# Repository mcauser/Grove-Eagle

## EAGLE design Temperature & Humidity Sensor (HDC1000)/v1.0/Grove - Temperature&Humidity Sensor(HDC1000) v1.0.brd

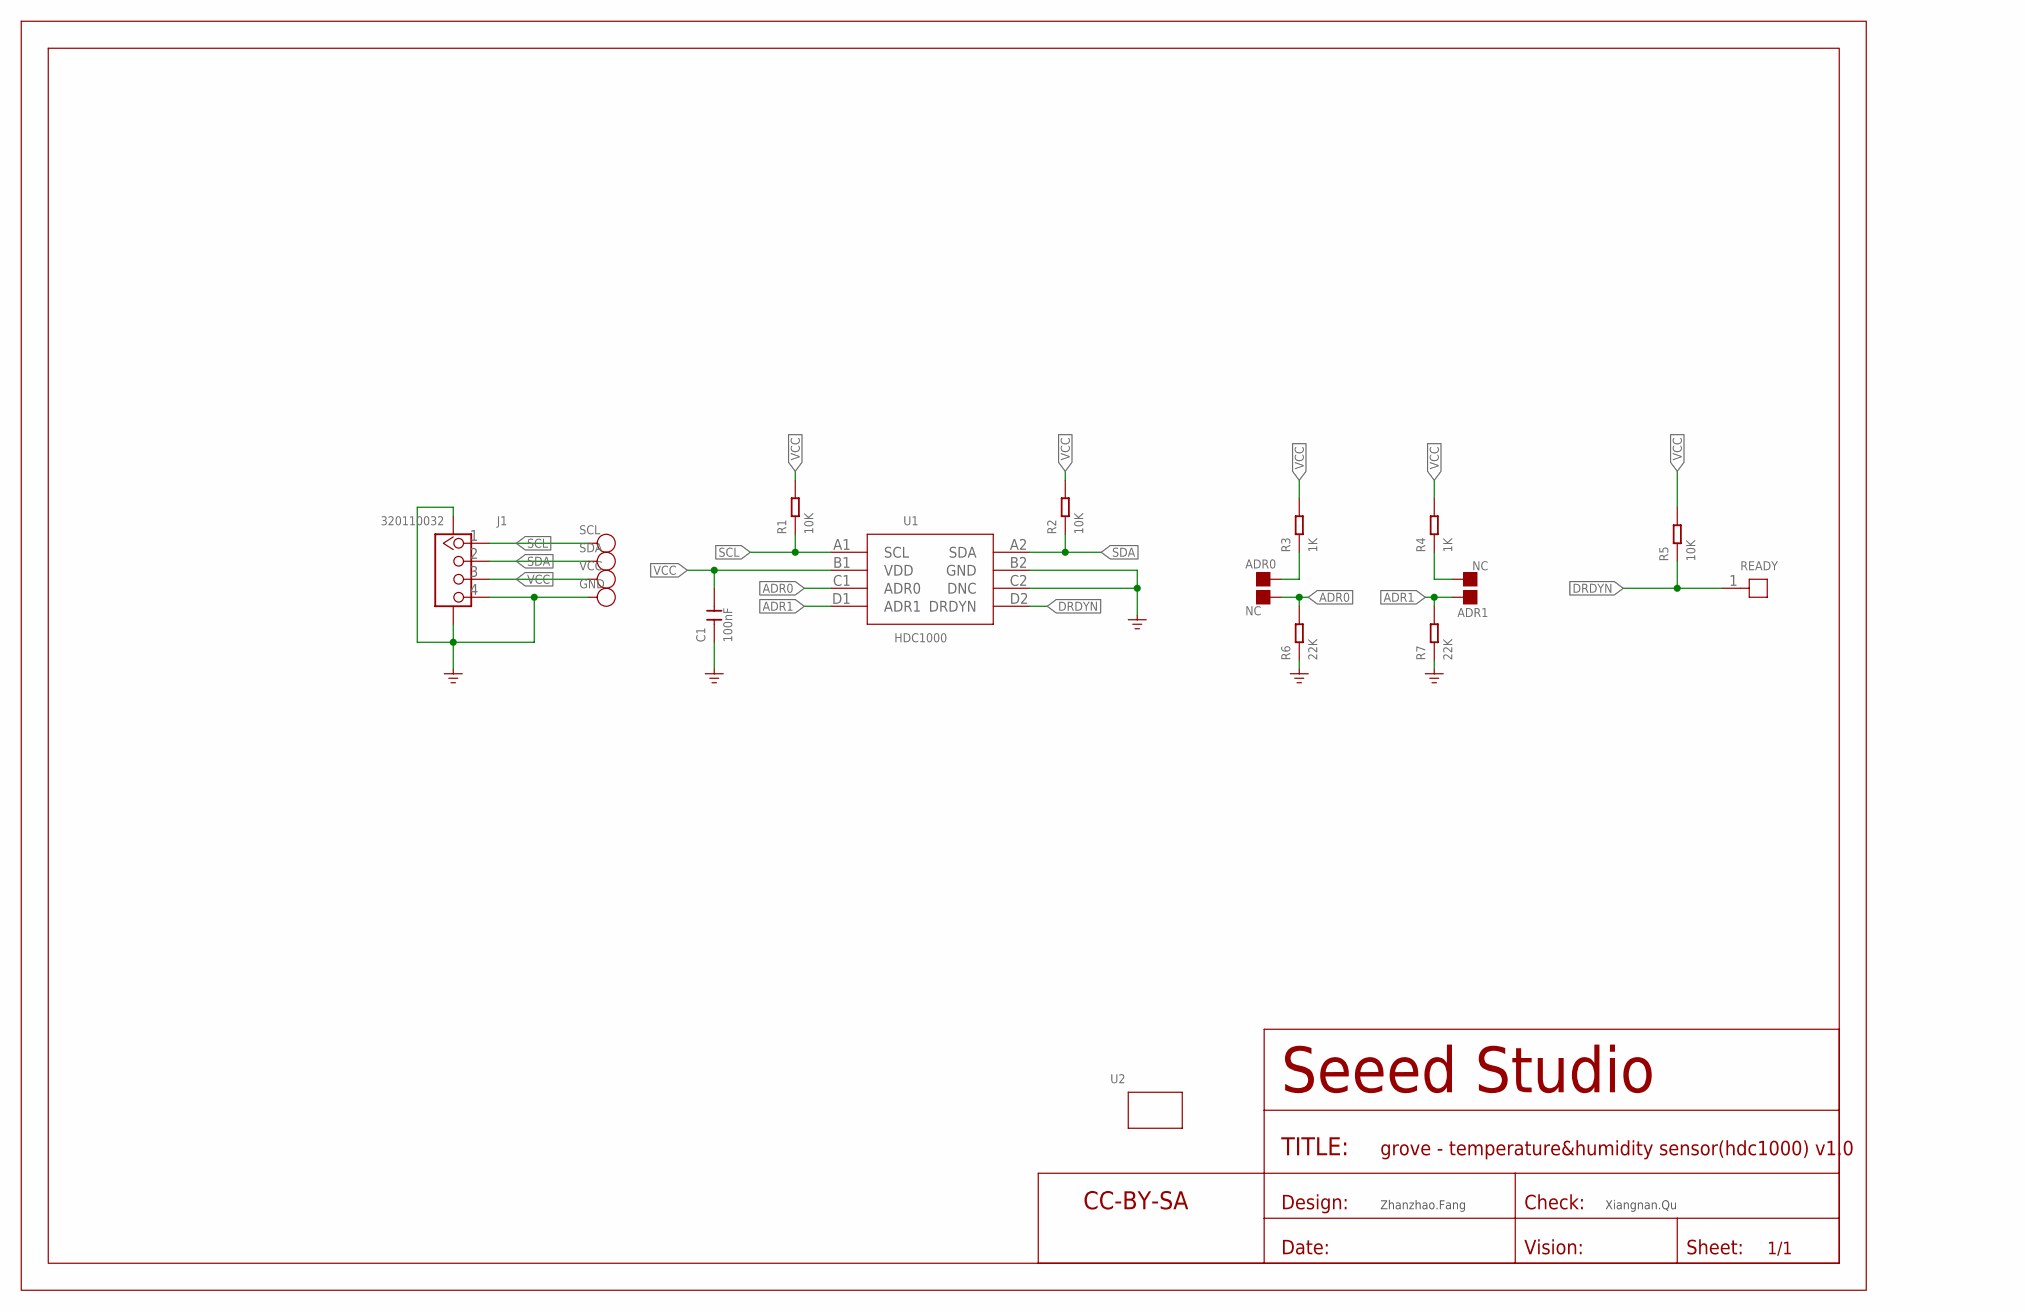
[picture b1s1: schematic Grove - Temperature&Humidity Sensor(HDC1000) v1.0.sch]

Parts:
ADR0, ADR1: NC; JUMPER-2P
C1: 100nF; C0603
GND: NC; TP-D45MIL
J1: 320110032; HW4-SMD-2.0-90D
R1, R2, R5: 10K; R0603
R3, R4: 1K; R0603
R6, R7: 22K; R0603
READY: HEADER-1P-40; 1P-80/40MIL
SCL: NC; TP-D45MIL
SDA: NC; TP-D45MIL
U1: HDC1000; SNR8-SMD-0.5-2.04X1.59MM
U2: GROVE'2U'; GROVE-1*2-TEST-PLATFORM
U$4: SEEEDSTUDIO-OPEN-SCH-FRAME; SEEEDSTUDIO-PCB-FRAME
VCC: NC; TP-D45MIL

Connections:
ADR0: ADR0.1, R6.2, U1.C1 (ADR0)
ADR1: ADR1.2, R7.2, U1.D1 (ADR1)
DRDYN: R5.1, READY.1, U1.D2 (DRDYN)
GND: C1.1, GND.T, J1.4, J1.SS1, J1.SS2, R6.1, R7.1, U1.B2 (GND), U1.C2 (DNC)
unnamed: ADR0.2, R3.1
unnamed: ADR1.1, R4.1
SCL: J1.1, R1.1, SCL.T, U1.A1 (SCL)
SDA: J1.2, R2.1, SDA.T, U1.A2 (SDA)
VCC: C1.2, J1.3, R1.2, R2.2, R3.2, R4.2, R5.2, U1.B1 (VDD), VCC.T

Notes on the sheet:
Zhanzhao.Fang
Xiangnan.Qu

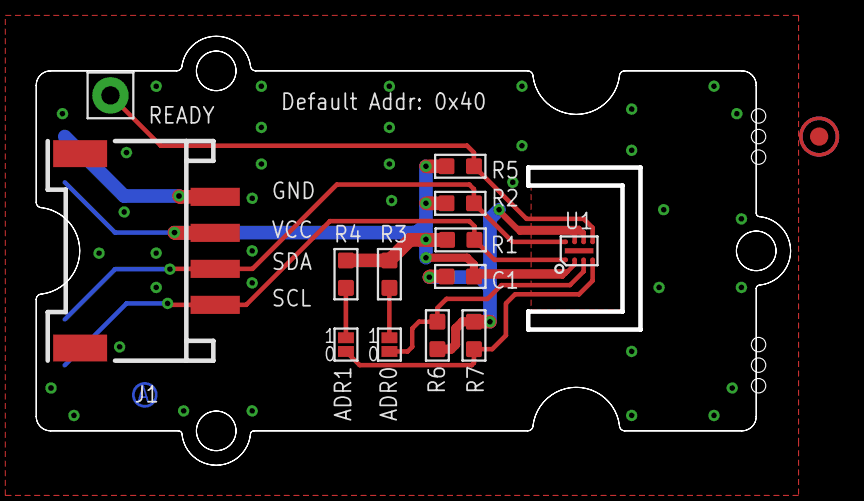
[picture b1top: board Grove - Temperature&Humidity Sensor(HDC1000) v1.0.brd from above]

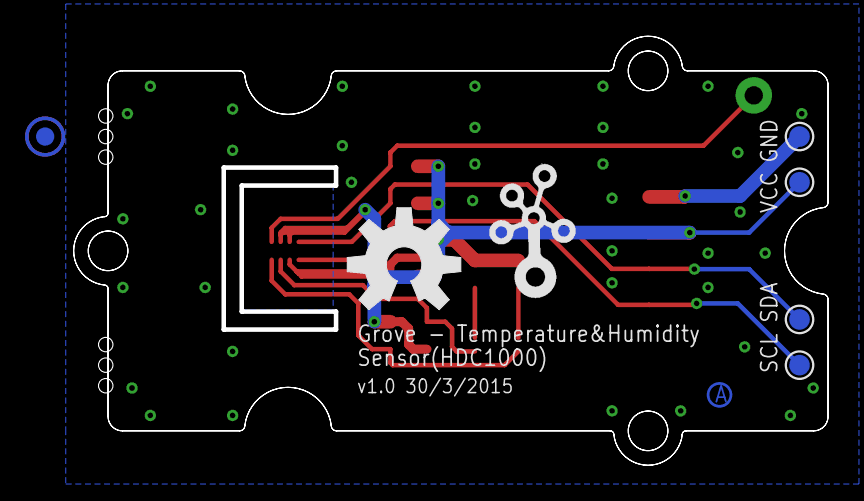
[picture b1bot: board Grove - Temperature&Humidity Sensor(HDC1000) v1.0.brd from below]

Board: 2 copper layers, 41.9 x 23.8 mm, 24 parts (7 on the bottom side), 9 nets.

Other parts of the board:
P4, P7: ROUND-MARK-1.0
U10: GROVE-TEST-PLATFORM
U$7: GROVE-SILK-BIG
U$10: OSHW_FILLX250_NOTEXT

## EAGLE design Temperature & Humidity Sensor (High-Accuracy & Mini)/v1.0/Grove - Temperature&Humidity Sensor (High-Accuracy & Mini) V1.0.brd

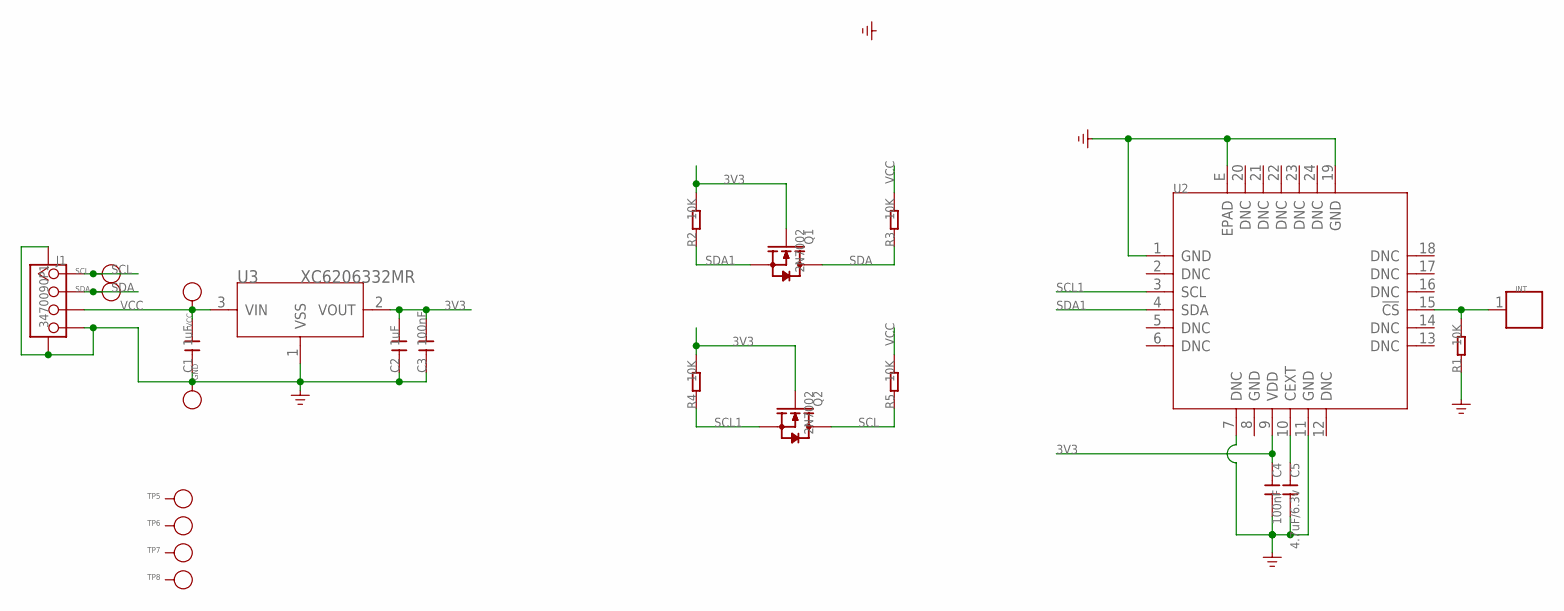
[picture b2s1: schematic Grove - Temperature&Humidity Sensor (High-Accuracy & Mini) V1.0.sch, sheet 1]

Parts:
C1, C2: 1uF; C0603
C3, C4: 100nF; C0603
C5: 4.7uF/6.3v; C0603
GND: PAD-TEST-POINT'4545'; TP_4545
INT: PAD'60/30'; 1P-65/35MIL
J1: 3470090P1; 4P-SMD-2.0
Q1, Q2: 2N7002; SOT23
R1, R2, R3, R4, R5: 10K; R0603
SCL: PAD-TEST-POINT'4545'; TP_4545
SDA: PAD-TEST-POINT'4545'; TP_4545
TP5, TP6, TP7, TP8: PAD-TEST-POINT'4545'; TP_4545
U2: SENSOR-TH02; QFN24
U3: XC6206332MR; SOT23
VCC: PAD-TEST-POINT'4545'; TP_4545

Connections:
3V3: C2.2, C3.2, C4.1, Q1.1 (G), Q2.1 (G), R2.2, R4.2, U2.9 (VDD), U3.2 (VOUT)
GND: C1.1, C2.1, C3.1, C4.2, C5.2, GND.T, J1.4, J1.SS1, J1.SS2, R1.1, U2.1 (GND), U2.7 (DNC), U2.11 (GND), U2.19 (GND), U2.E (EPAD), U3.1 (VSS)
unnamed: C5.1, U2.10 (CEXT)
unnamed: INT.1, R1.2, U2.15 (!CS)
SCL: J1.1, Q2.3 (D), R5.1, SCL.T
SCL1: Q2.2 (S), R4.1, U2.3 (SCL)
SDA: J1.2, Q1.3 (D), R3.1, SDA.T
SDA1: Q1.2 (S), R2.1, U2.4 (SDA)
VCC: C1.2, J1.3, R3.2, R5.2, U3.3 (VIN), VCC.T

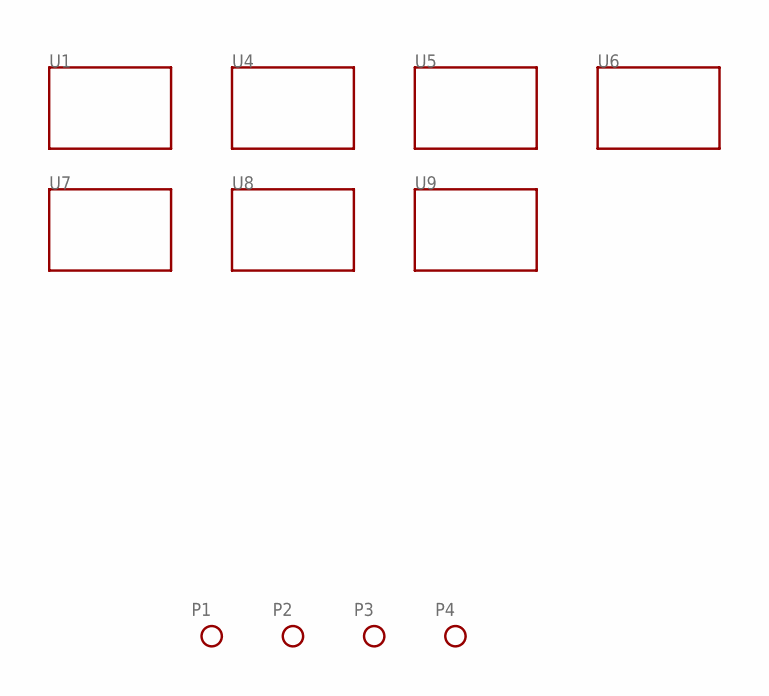
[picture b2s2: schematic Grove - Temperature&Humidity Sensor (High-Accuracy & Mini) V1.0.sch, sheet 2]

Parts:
P1, P2, P3, P4: PAD-MARK; ROUND-MARK-1.0
U1, U4, U5, U6, U7, U8, U9: TWIG'2U'; GROVE-TEST-PLATFORM

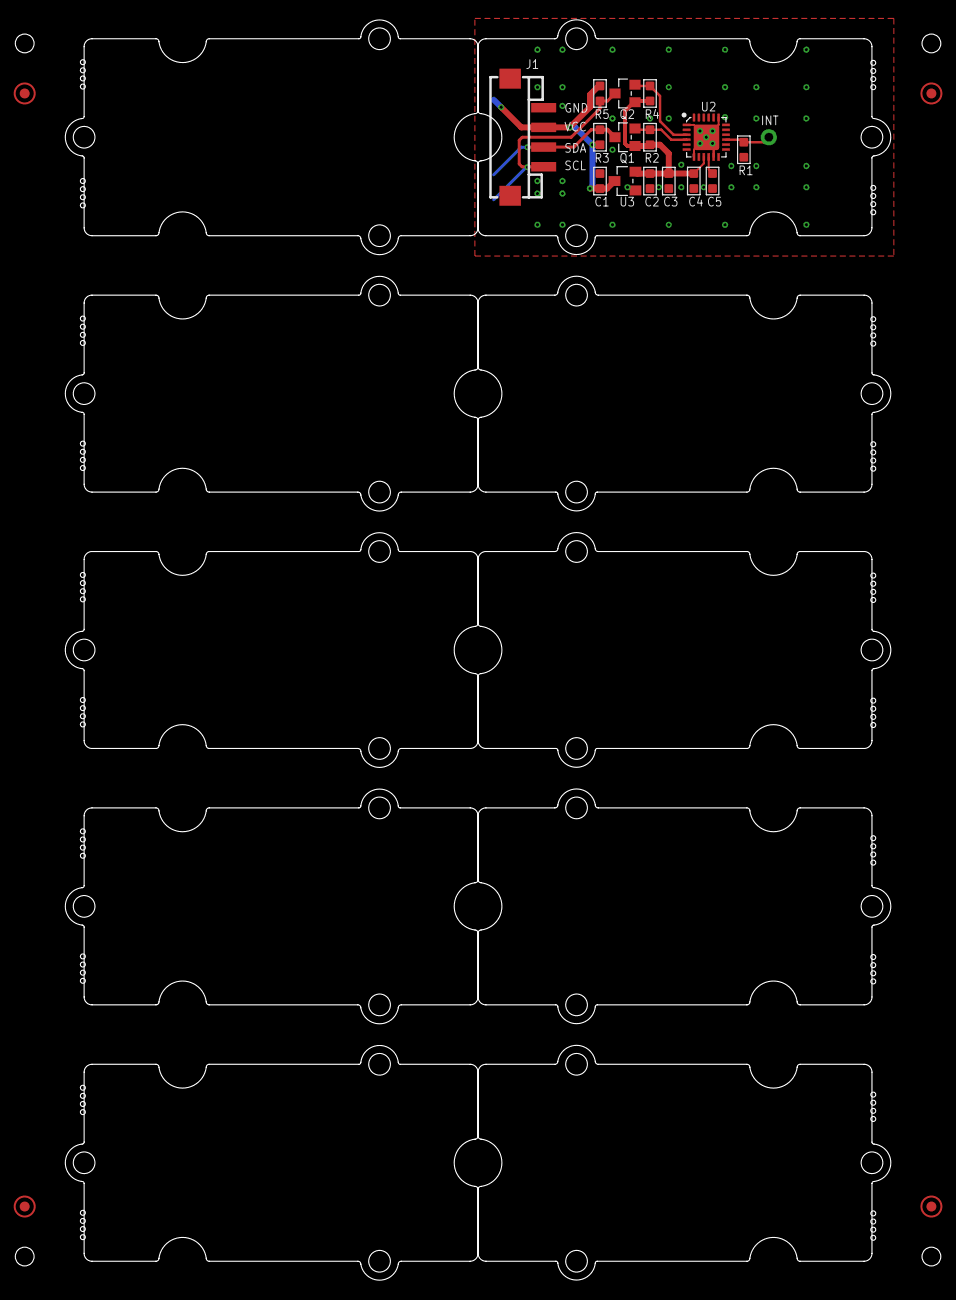
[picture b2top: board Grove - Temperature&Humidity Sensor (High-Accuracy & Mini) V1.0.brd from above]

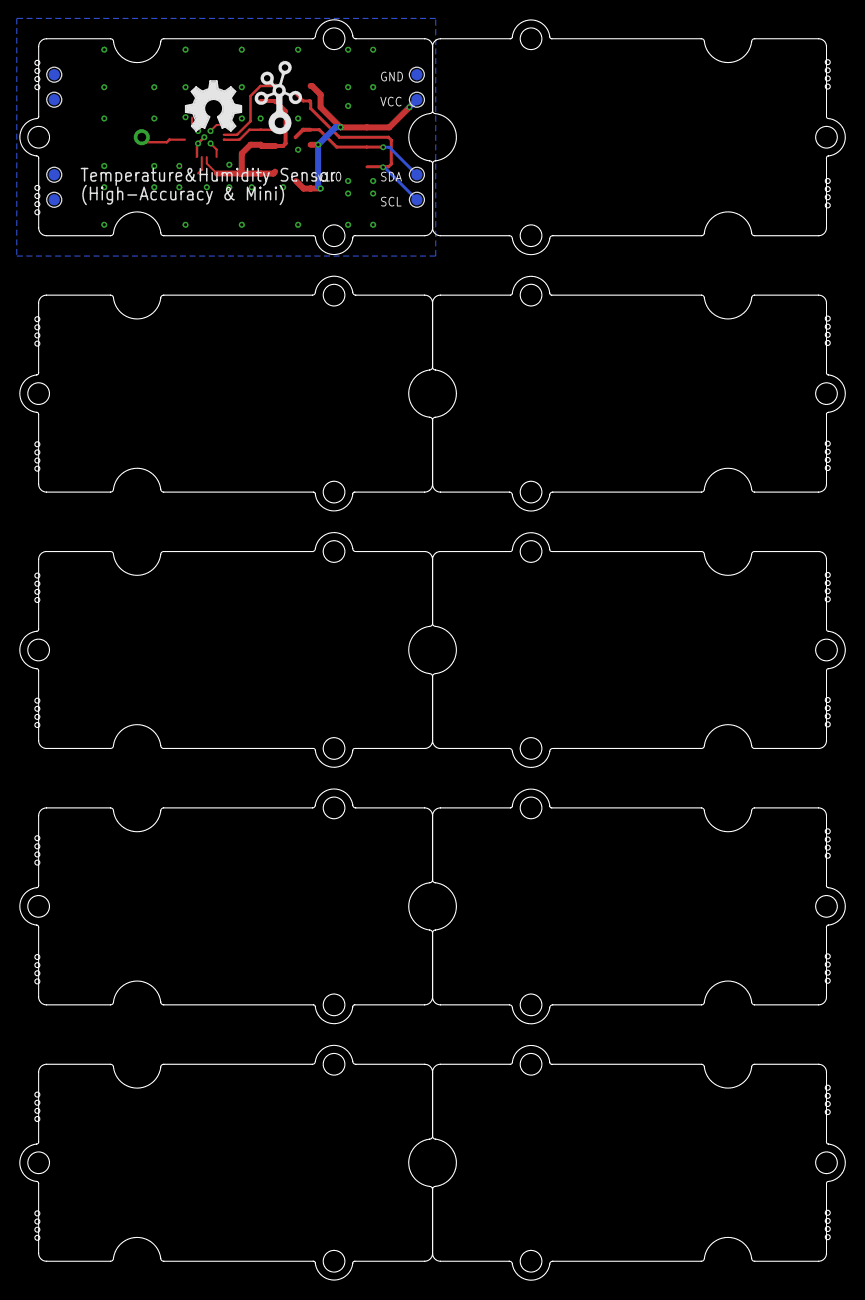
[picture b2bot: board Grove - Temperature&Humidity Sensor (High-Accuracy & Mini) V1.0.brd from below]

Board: 2 copper layers, 83.8 x 128.0 mm, 40 parts (10 on the bottom side), 9 nets.

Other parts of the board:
U11, U12: GROVE-TEST-PLATFORM@1
U$5: GROVE-2CONNECTOR-SMD
U$6: OSHW_FILLX200_NOTEXT
U$7: TWIGLOGO

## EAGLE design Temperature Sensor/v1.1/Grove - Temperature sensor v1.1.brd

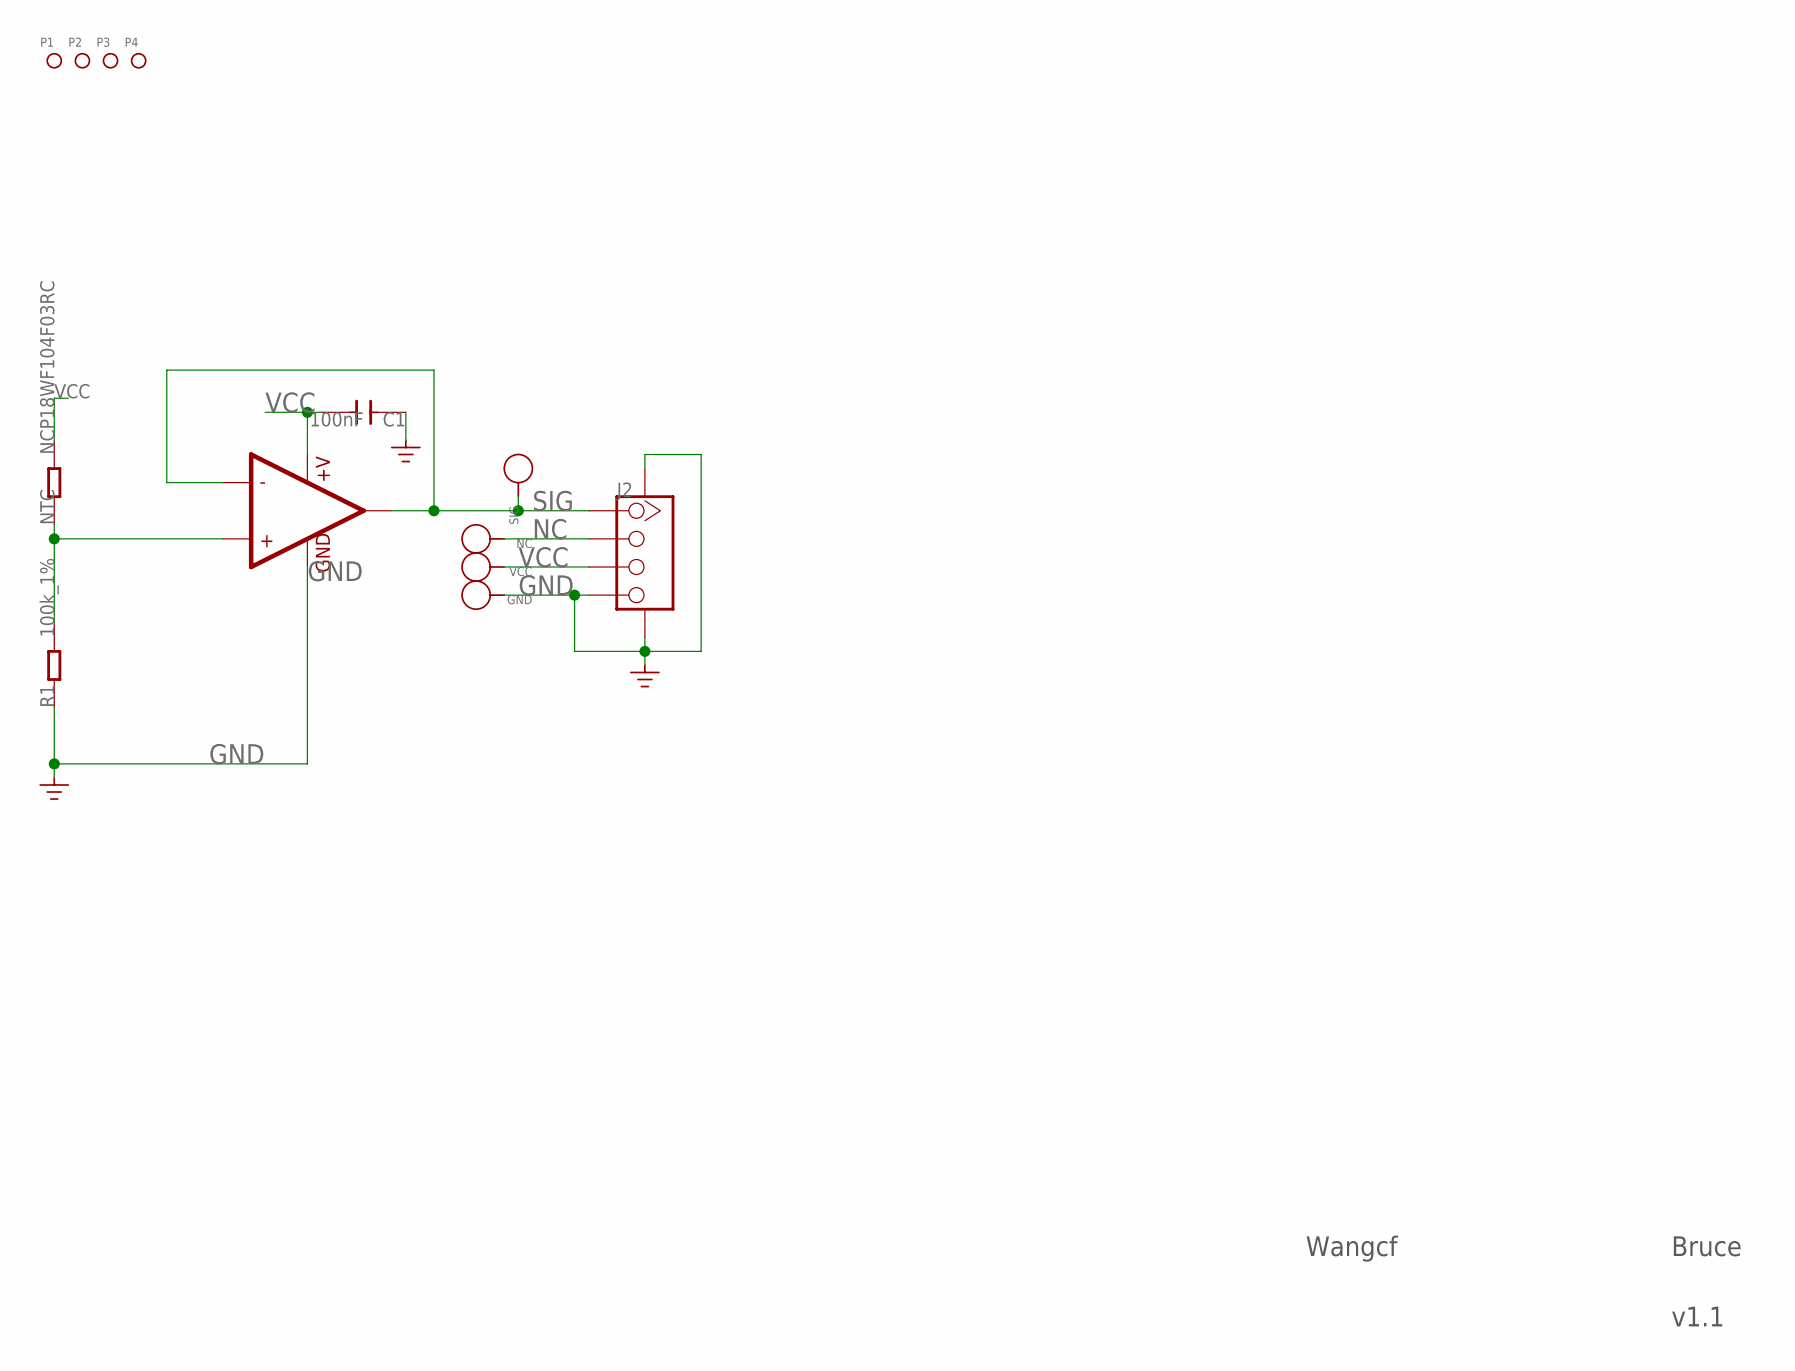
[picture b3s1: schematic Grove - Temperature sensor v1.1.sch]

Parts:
C1: 100nF; C0603
GND: PAD-TEST-POINT'4545'; TP_4545
J2: TWIG-4P-2.0-SMD-FEMALE-REINFORCE'DD'; 4P-SMD-2.0
NC: PAD-TEST-POINT'4545'; TP_4545
NTC: NCP18WF104F03RC; R0603
P1, P2, P3, P4: PAD-MARK; ROUND-MARK-1.0
R1: 100k_1%; R0603
SIG: PAD-TEST-POINT'4545'; TP_4545
U1: LM358DR; SO08
VCC: PAD-TEST-POINT'4545'; TP_4545

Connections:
GND: C1.1, GND.T, J2.4, J2.SS1, J2.SS2, R1.1, U1.4 (GND)
unnamed: NTC.1, R1.2, U1.3 (+IN1)
NC: J2.2, NC.T
SIG: J2.1, SIG.T, U1.1 (OUT1), U1.2 (-IN1)
VCC: C1.2, J2.3, NTC.2, U1.8 (+V), VCC.T

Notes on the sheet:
Wangcf
Bruce
v1.1

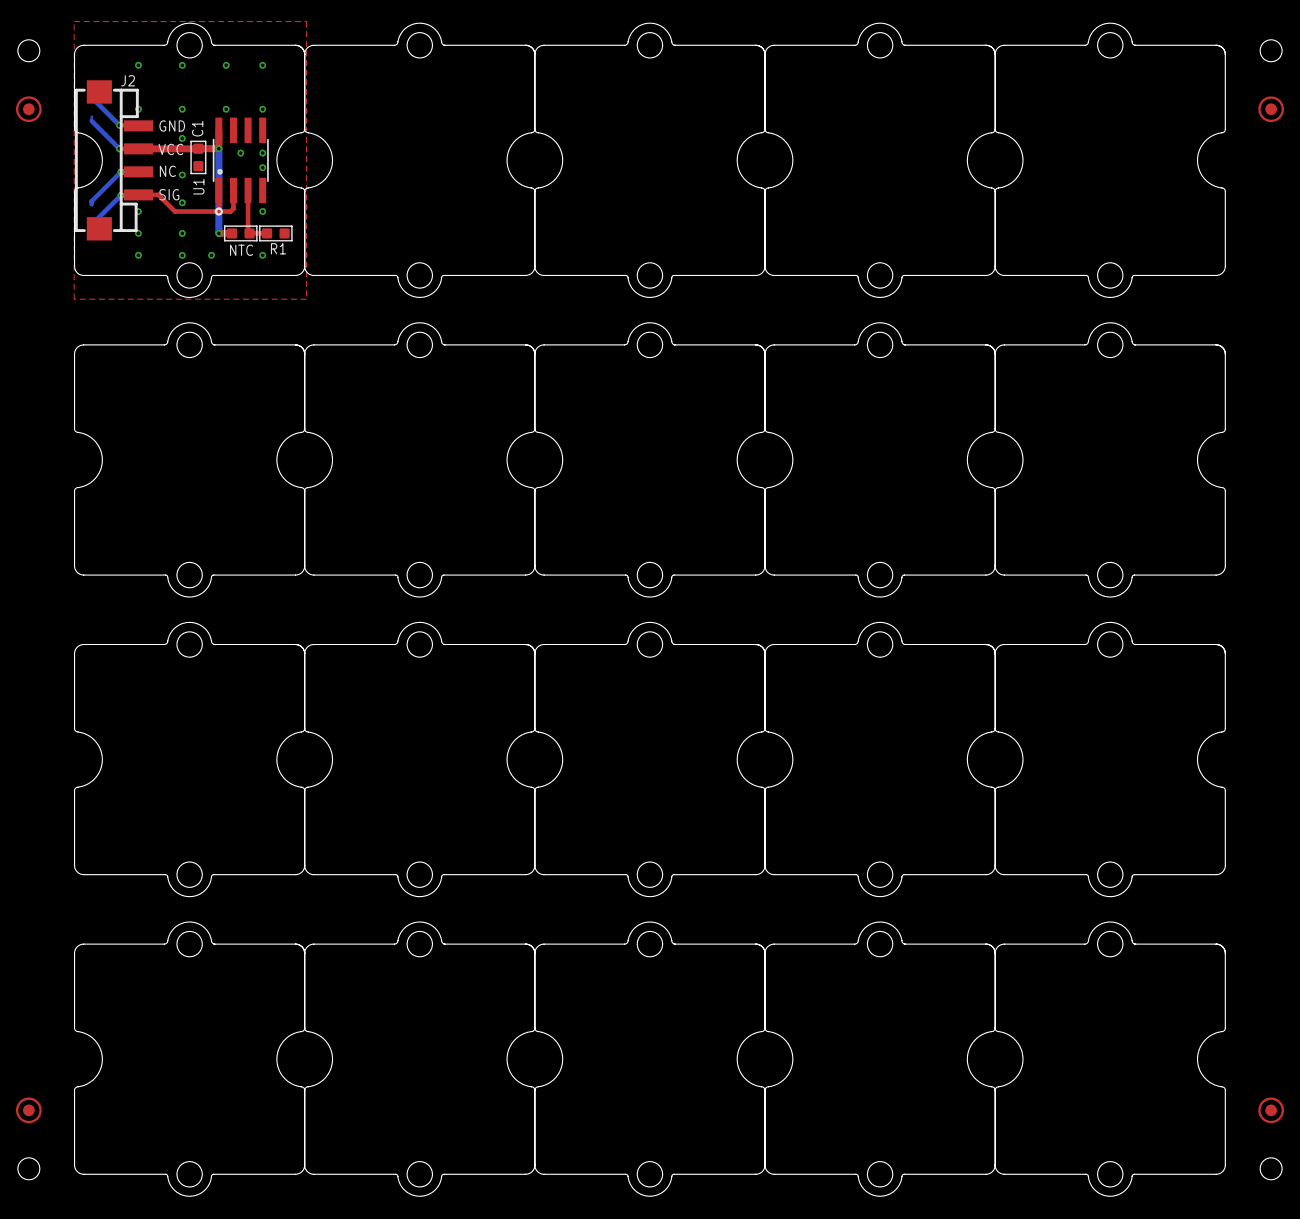
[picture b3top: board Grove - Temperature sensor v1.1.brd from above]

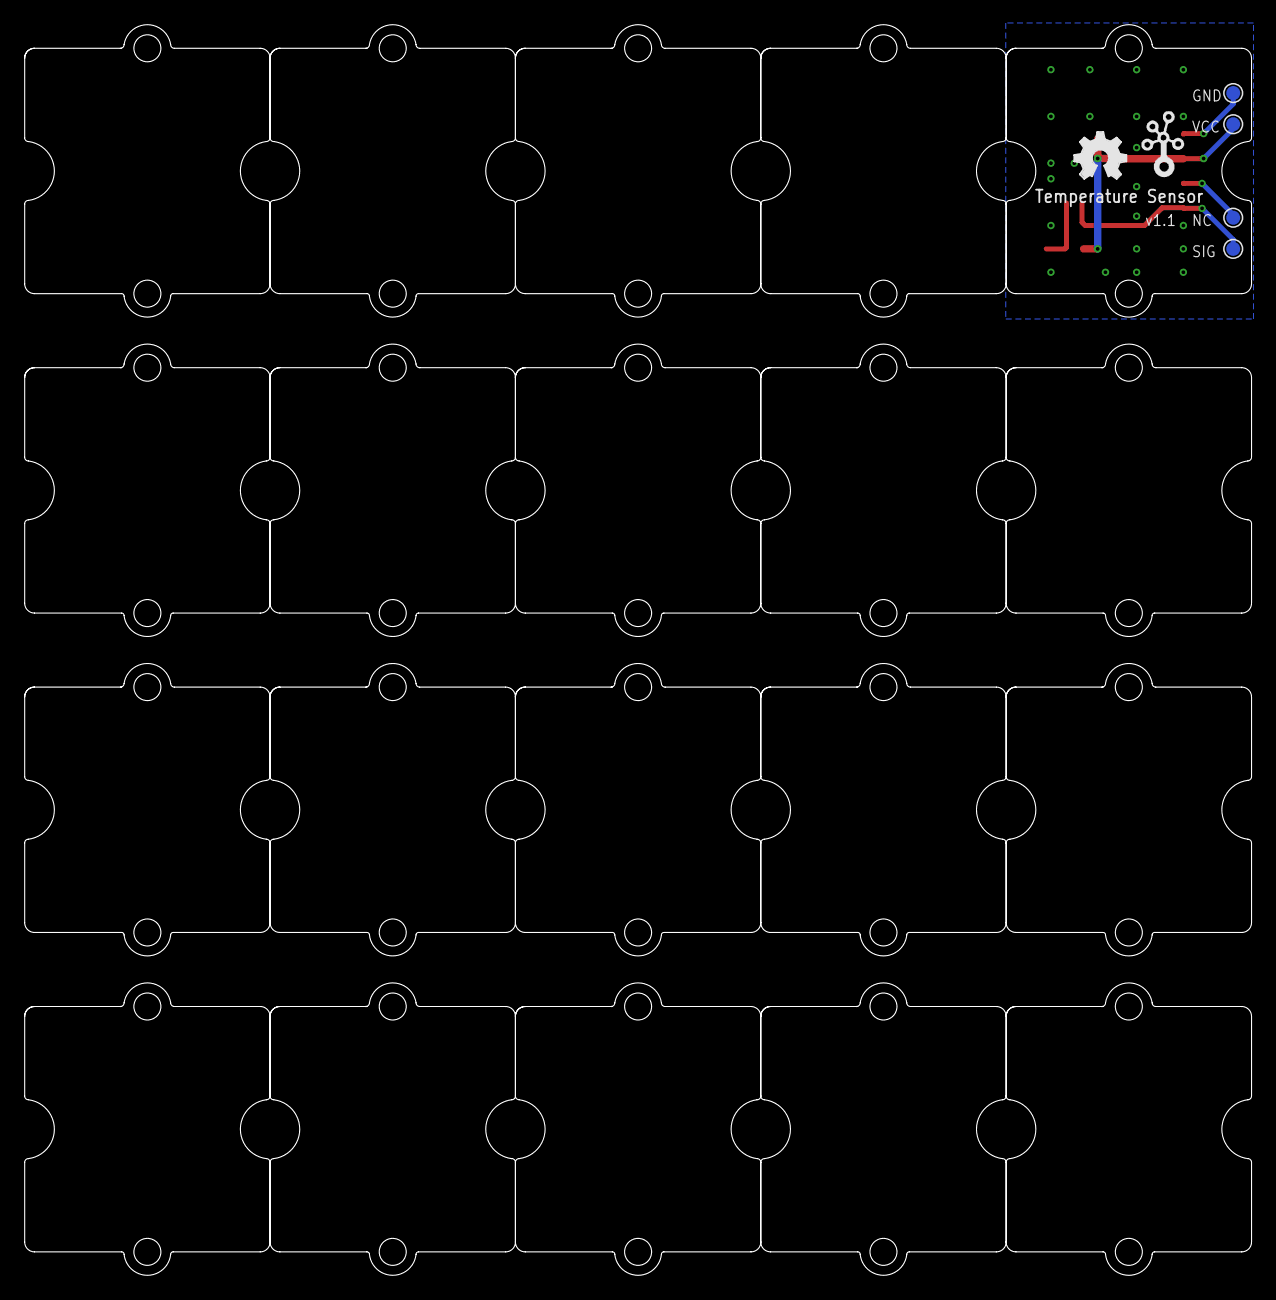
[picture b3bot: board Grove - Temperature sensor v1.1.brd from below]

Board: 2 copper layers, 100.0 x 101.9 mm, 35 parts (6 on the bottom side), 5 nets.

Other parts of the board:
U$4, U$10, U$11, U$12, U$13, U$14, U$15, U$16, U$17, U$18, U$19, U$20, U$21, U$22, U$23, U$24, U$25, U$26, U$27, U$28: 1U-DIM-W/-DRILL
U$6: TWIGLOGO_SMALL
U$7: OSHW_FILLX150_NOTEXT

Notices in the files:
parts and their libraries:
moudle-new: This work is licensed under the Creative Commons Attribution 4.0 International License.
To view a copy of this license,visit:
http://creativecommons.org/licenses/by-sa/4.0
moudle-new: CC-BY-SA
